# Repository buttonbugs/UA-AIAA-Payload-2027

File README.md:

# UA AIAA Payload 2027

This repository includes the payload codes for the [UA AIAA](https://uaaiaa.org/) Rocket Competition Team.

## Software

**VS Code Extension:** [PlatformIO IDE](https://marketplace.visualstudio.com/items?itemName=platformio.platformio-ide)

**Framework:** Arduino

### Libraries

| Libraries             | Installation                  |
| -                     | -                             |
| DFRobot_OzoneSensor   | [DFRobot Website](https://wiki.dfrobot.com/Gravity_IIC_Ozone_Sensor_(0-10ppm)%20SKU_SEN0321) |
| ICM_20948             | PlatformIO &rarr; Libraries   |
| Adafruit_BME280       | PlatformIO &rarr; Libraries   |
| SD                    | PlatformIO &rarr; Libraries   |
| Adafruit_SGP40        | PlatformIO &rarr; Libraries   |
| WatchDog              | [Arduino Built-In Library](https://docs.arduino.cc/libraries/watchdog/) |

## Hardware

### Pin Configuration

**Pin Configuration for I²C and SPI**

| Pin Name | Pin No.| Protocol |
| - | - | - |
| SDA | A4 | I²C |
| SCL | A5 | I²C |
| CLK / SCK | D13 | SPI |
| DO / MISO | D12 | SPI |
| DI / MOSI | D11 | SPI |
| CS for the SD Card Reader | D10 (or any) | SPI |

**Pin Configuration for Ultrasonic Sensor**

| Sensor | Trigger Pin | Echo Pin |
| - | - | - |
| Ultrasonic Sensor 1 | D2 | D3 |
| Ultrasonic Sensor 2 | D4 | D5 |
| Ultrasonic Sensor 3 | D6 | D7 |

**Other Pin Configuration**

| Sensor | Signal Pin |
| - | - |
| SW-18010P 1 (Horizontal)  | A6 |
| SW-18010P 2 (Vertical)    | A7 |

Reference: [Arduino Nano Every Full Pinout Diagram (Official)](https://content.arduino.cc/assets/Pinout-NANOevery_latest.pdf)

### Electronics

| Electronics | Description | Voltage | Protocol | On PCB |
| - | - | - | - | - |
| Microcontroller | [Arduino Nano Every](https://store-usa.arduino.cc/products/nano-every) | 5V | - | Y |
| SD Card Reader | [Adafruit MicroSD Card Breakout ADA254](https://www.amazon.com/Adafruit-MicroSD-Breakout-Board-ADA254/dp/B00NAY2NAI/) | 5V | SPI | Y |
| Ozone Sensor | [DFRobot Gravity: IIC Ozone Sensor V1.0](https://wiki.dfrobot.com/Gravity_IIC_Ozone_Sensor_(0-10ppm)%20SKU_SEN0321) | 3.3V - 5.5V | I²C | N |
| VOC Sensor | [Waveshare SGP40 VOC Sensor](https://www.waveshare.com/wiki/SGP40_VOC_Sensor#Test_the_codes) | 3.3V or 5V | I²C | N |
| IMU Sensor | [SparkFun 9DoF IMU Breakout - ICM 20948](https://www.amazon.com/SparkFun-Breakout-ICM-20948-connection-Accelerometer-Magnetometer/dp/B07VNV3WKL/) | 1.95 V - 3.6 V | I²C | Y |
| BME280 Sensor | [Starry GY-BME280 5V](https://www.amazon.com/Starry-Atmospheric-Pressure-Temperature-GY-BME280/dp/B0DRCNNBF3/) | 5V | I²C | Y |
| Ultrasonic Sensor | HC-SR04 | 5V | - | N |
| Vibration Sensor | [SW-18020P](https://www.adafruit.com/product/2384) | &le; 12V | - | N |

## PCB

### PCB resources

Arduino footprints and symbols: [Alarm-Siren/arduino-kicad-library](https://github.com/Alarm-Siren/arduino-kicad-library)

PCB manufacturer: [JLCPCB](https://jlcpcb.com/)

### How to generate Gerber and Drill files in KiCAD 9

See https://jlcpcb.com/help/article/how-to-generate-gerber-and-drill-files-in-kicad-9

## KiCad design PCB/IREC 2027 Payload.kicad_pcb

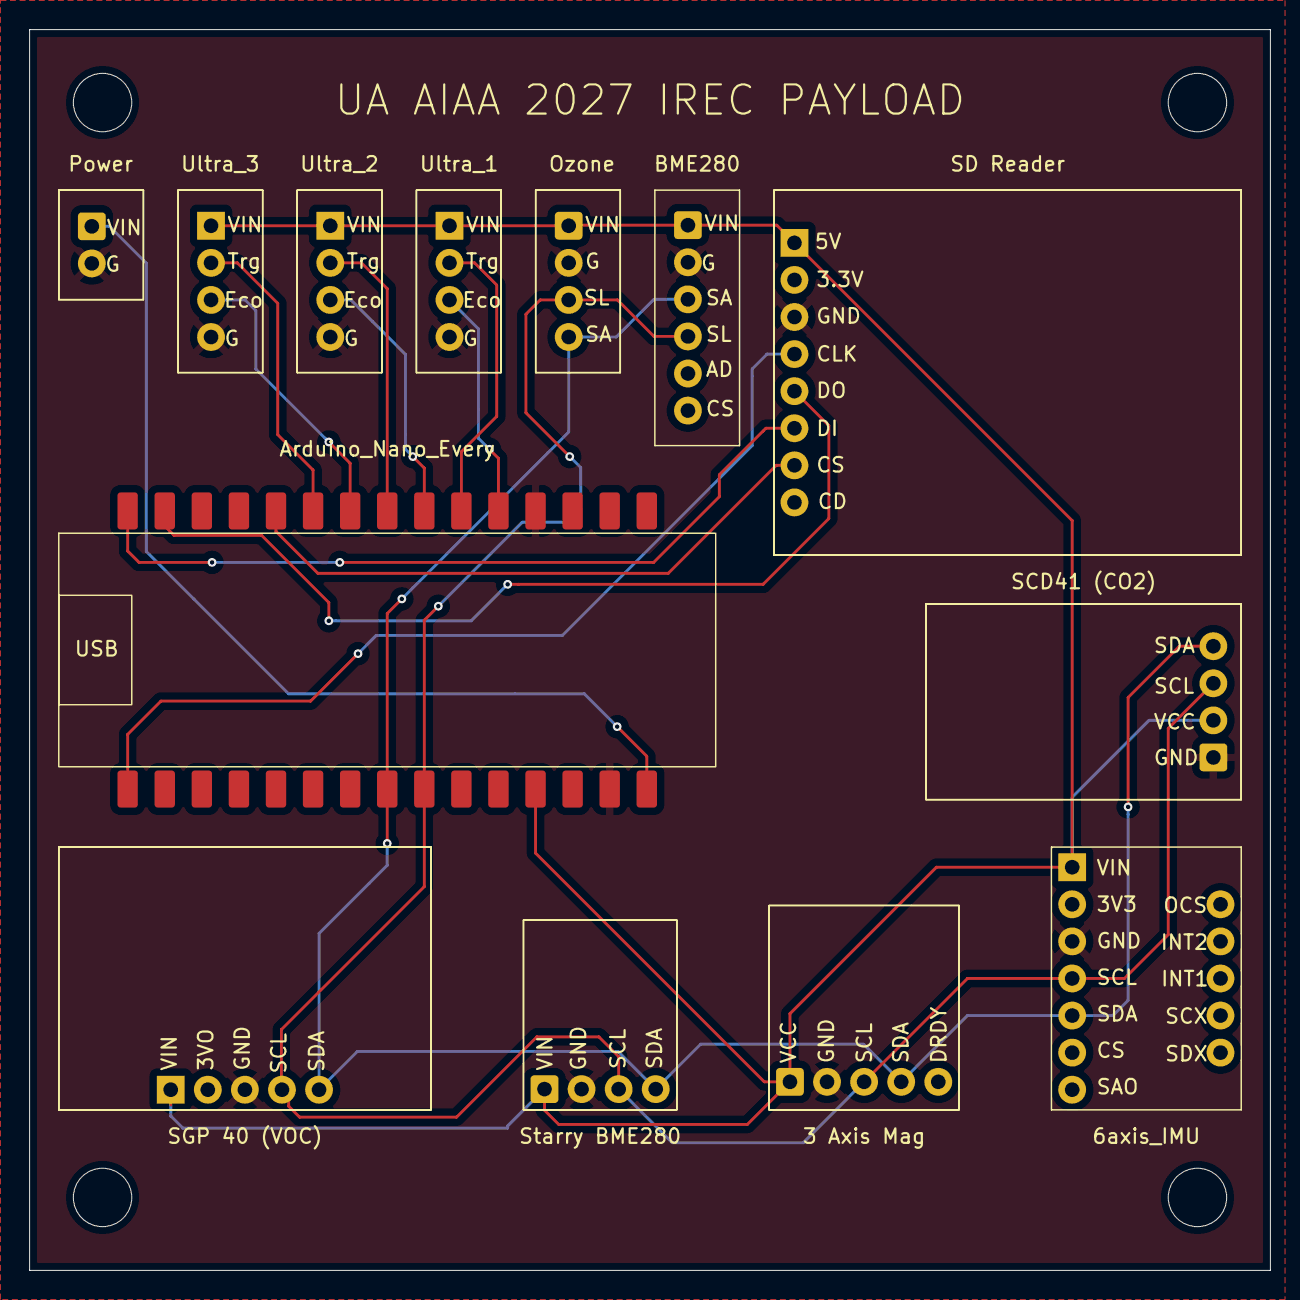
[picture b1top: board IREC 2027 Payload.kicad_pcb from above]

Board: 2 copper layers, 85.0 x 85.0 mm, 13 parts (0 on the bottom side), 15 nets.

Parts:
A1: Arduino_Nano_Every; SMD_Arduino
J1: Power
U1: Ultra_1; Ultrasonic
U2: Ultra_2; Ultrasonic
U3: Ultra_3; Ultrasonic
U4: SD Reader; SD_Reader
U5: BME280; BME_280
U6: 6axis_IMU; 6_Axis_IMU
U7: Ozone
U8: SCD41 (CO2); SDC_41
U9: SGP 40 (VOC); SGP_40
U10: Starry BME280; Starry_BME_280
U11: 3 Axis Mag; 3_Axis_Mag

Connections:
+5V: A1.27 (+5V), U1.1 (VCC), U2.1 (VCC), U3.1 (VCC), U4.1 (VCC), U5.1 (VCC), U6.1 (VCC), U7.1 (VCC), U8.2 (VCC), U9.1 (VCC), U10.1 (VCC), U11.1 (VCC)
+5VA: A1.30 (VIN), J1.1
GND: A1.4 (GND), A1.29 (GND), J1.2, U1.4 (GND), U2.4 (GND), U3.4 (GND), U4.3 (GND), U5.2 (GND), U6.3 (GND), U7.2 (GND), U8.1 (GND), U9.3 (GND), U10.2 (GND), U11.2 (GND)
unnamed: A1.5 (D2), U1.3 (ECHO)
unnamed: A1.6 (D3), U1.2 (TRIG)
unnamed: A1.7 (D4), U2.3 (ECHO)
unnamed: A1.8 (D5), U2.2 (TRIG)
unnamed: A1.9 (D6), U3.3 (ECHO)
unnamed: A1.10 (D7), U3.2 (TRIG)
unnamed: A1.11 (D8), U4.7 (CS)
unnamed: A1.15 (MISO), U4.6 (DI)
unnamed: A1.14 (MOSI), U4.5 (DO)
unnamed: A1.16 (SCK), U4.4 (CLK)
unnamed: A1.24 (SCL/A5), U5.4 (SCL), U6.4 (SCL), U7.3 (SCL), U8.3 (SCL), U9.4 (SCL), U10.3 (SCL), U11.3 (SCL)
unnamed: A1.23 (SDA/A4), U5.3 (SDA), U6.5 (SDA), U7.4 (SDA), U8.4 (SDA), U9.5 (SDA), U10.4 (SDA), U11.4 (SDA)
